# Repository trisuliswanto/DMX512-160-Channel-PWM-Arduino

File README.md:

# DMX512-160-Channel-PWM-Arduino

PCB files for the DMX512-160-Channel-PWM-Arduino

Format is KiCad schematic and board layout
for more information please visit:
  * http://trisuliswanto.com
  
Designed by Tri Suliswanto From Tuban, Jawa Timur, Indonesia.  
GNU GPLv3 license, check LICENSE for more information
All text above must be included in any redistribution

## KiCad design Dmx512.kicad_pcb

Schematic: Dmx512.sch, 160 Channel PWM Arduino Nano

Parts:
A1: Arduino_Nano_v3.x; Arduino_Nano
C11, C12, C13: 4700uF; CP_Radial_D22.0mm_P10.00mm_SnapIn
C14: 10uF; C_0805_2012Metric_Pad1.15x1.40mm_HandSolder
J1: DMX; TerminalBlock_bornier-3_P5.08mm
J13: Screw_Terminal_01x02; TerminalBlock_RND_205-00067_1x02_P7.50mm_Horizontal
R1, R2, R3, R4, R5: 10K; R_0805_2012Metric_Pad1.15x1.40mm_HandSolder
R6, R7: 20K; R_0805_2012Metric_Pad1.15x1.40mm_HandSolder
R8: 120; R_0805_2012Metric_Pad1.15x1.40mm_HandSolder
U1: MAX485E; SO-8_5.3x6.2mm_P1.27mm

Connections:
DERE: A1.5, R4.2, U1.2 (~RE), U1.3 (DE)
GND: A1.4, A1.29, C11.2, C12.2, C13.2, C14.2, J1.3, J13.1, R6.1, U1.5 (GND); also elsewhere on the board
unnamed: J1.1, R6.2, R8.2, U1.7 (B)
unnamed: J1.2, R7.2, R8.1, U1.6 (A)
OE: A1.6; also elsewhere on the board
RXD: A1.2, R5.2, U1.1 (RO)
SCL: A1.24, R1.2; also elsewhere on the board
SDA: A1.23, R2.2; also elsewhere on the board
TXD: A1.1, R3.2, U1.4 (DI)
VCC: A1.27, C11.1, C12.1, C13.1, C14.1, J13.2, R1.1, R2.1, R3.1, R4.1, R5.1, R7.1, U1.8 (VCC); also elsewhere on the board

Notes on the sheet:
DMX RS485
Arduino Nano
Capacitor
PWM IC BLOCK

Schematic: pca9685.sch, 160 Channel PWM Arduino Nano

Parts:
C1: 10uF; C_0805_2012Metric_Pad1.15x1.40mm_HandSolder
D1, D2, D3, D4, D5, D6, D7, D8, D9, D10, D11, D12, D13, D14, D15, D16: LED; LED_D3.0mm
J3: Conn_01x16; PinHeader_1x16_P2.54mm_Vertical
JP1, JP2, JP3, JP4, JP5, JP6: JP; C_0603_1608Metric
R9, R10, R11, R12, R13, R14, R15: 10K; R_0805_2012Metric_Pad1.15x1.40mm_HandSolder
R16, R17, R18, R19, R20, R21, R22, R23, R24, R25, R26, R27, R28, R29, R30, R31: 330; R_0805_2012Metric_Pad1.15x1.40mm_HandSolder
U2: PCA9685PW; TSSOP-28_4.4x9.7mm_P0.65mm

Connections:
/pca9685/LED0: J3.1, R16.2, U2.6
/pca9685/LED1: J3.2, R17.2, U2.7
/pca9685/LED2: J3.3, R18.2, U2.8
/pca9685/LED3: J3.4, R19.2, U2.9
/pca9685/LED4: J3.5, R20.2, U2.10
/pca9685/LED5: J3.6, R21.2, U2.11
/pca9685/LED6: J3.7, R22.2, U2.12
/pca9685/LED7: J3.8, R23.2, U2.13
/pca9685/LED8: J3.9, R24.2, U2.15
/pca9685/LED9: J3.10, R25.2, U2.16
/pca9685/LED10: J3.11, R26.2, U2.17
/pca9685/LED11: J3.12, R27.2, U2.18
/pca9685/LED12: J3.13, R28.2, U2.19
/pca9685/LED13: J3.14, R29.2, U2.20
/pca9685/LED14: J3.15, R30.2, U2.21
/pca9685/LED15: J3.16, R31.2, U2.22
GND: C1.2, R9.1, R10.1, R11.1, R12.1, R13.1, R14.1, R15.2, U2.14, U2.25; also elsewhere on the board
unnamed: D1.1, R16.1
unnamed: D2.1, R17.1
unnamed: D3.1, R18.1
unnamed: D4.1, R19.1
unnamed: D5.1, R20.1
unnamed: D6.1, R21.1
unnamed: D7.1, R22.1
unnamed: D8.1, R23.1
unnamed: D9.1, R24.1
unnamed: D10.1, R25.1
unnamed: D11.1, R26.1
unnamed: D12.1, R27.1
unnamed: D13.1, R28.1
unnamed: D14.1, R29.1
unnamed: D15.1, R30.1
unnamed: D16.1, R31.1
unnamed: JP1.2, R9.2, U2.1
unnamed: JP2.2, R10.2, U2.2
unnamed: JP3.2, R11.2, U2.3
unnamed: JP4.2, R12.2, U2.4
unnamed: JP5.2, R13.2, U2.5
unnamed: JP6.2, R14.2, U2.24
OE: R15.1, U2.23; also elsewhere on the board
SCL: U2.26; also elsewhere on the board
SDA: U2.27; also elsewhere on the board
VCC: C1.1, D1.2, D2.2, D3.2, D4.2, D5.2, D6.2, D7.2, D8.2, D9.2, D10.2, D11.2, D12.2, D13.2, D14.2, D15.2, D16.2, JP1.1, JP2.1, JP3.1, JP4.1, JP5.1, JP6.1, U2.28; also elsewhere on the board

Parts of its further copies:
C2, C3, C4, C5, C6, C7, C8, C9, C10: 10uF; C_0805_2012Metric_Pad1.15x1.40mm_HandSolder
D17, D18, D19, D20, D21, D22, D23, D24, D25, D26, D27, D28, D29, D30, D31, D32, D33, D34, D35, D36, D37, D38, D39, D40, D41, D42, D43, D44, D45, D46, D47, D48, D49, D50, D51, D52, D53, D54, D55, D56, D57, D58, D59, D60, D61, D62, D63, D64, D65, D66, D67, D68, D69, D70, D71, D72, D73, D74, D75, D76, D77, D78, D79, D80, D81, D82, D83, D84, D85, D86, D87, D88, D89, D90, D91, D92, D93, D94, D95, D96, D97, D98, D99, D100, D101, D102, D103, D104, D105, D106, D107, D108, D109, D110, D111, D112, D113, D114, D115, D116, D117, D118, D119, D120, D121, D122, D123, D124, D125, D126, D127, D128, D129, D130, D131, D132, D133, D134, D135, D136, D137, D138, D139, D140, D141, D142, D143, D144, D145, D146, D147, D148, D149, D150, D151, D152, D153, D154, D155, D156, D157, D158, D159, D160: LED; LED_D3.0mm
J4, J5, J6, J7, J8, J9, J10, J11, J12: Conn_01x16; PinHeader_1x16_P2.54mm_Vertical
JP7, JP8, JP9, JP10, JP11, JP12, JP13, JP14, JP15, JP16, JP17, JP18, JP19, JP20, JP21, JP22, JP23, JP24, JP25, JP26, JP27, JP28, JP29, JP30, JP31, JP32, JP33, JP34, JP35, JP36, JP37, JP38, JP39, JP40, JP41, JP42, JP43, JP44, JP45, JP46, JP47, JP48, JP49, JP50, JP51, JP52, JP53, JP54, JP55, JP56, JP57, JP58, JP59, JP60: JP; C_0603_1608Metric
R32, R33, R34, R35, R36, R37, R38, R55, R56, R57, R58, R59, R60, R61, R78, R79, R80, R81, R82, R83, R84, R101, R102, R103, R104, R105, R106, R107, R124, R125, R126, R127, R128, R129, R130, R147, R148, R149, R150, R151, R152, R153, R170, R171, R172, R173, R174, R175, R176, R193, R194, R195, R196, R197, R198, R199, R216, R217, R218, R219, R220, R221, R222: 10K; R_0805_2012Metric_Pad1.15x1.40mm_HandSolder
R39, R40, R41, R42, R43, R44, R45, R46, R47, R48, R49, R50, R51, R52, R53, R54, R62, R63, R64, R65, R66, R67, R68, R69, R70, R71, R72, R73, R74, R75, R76, R77, R85, R86, R87, R88, R89, R90, R91, R92, R93, R94, R95, R96, R97, R98, R99, R100, R108, R109, R110, R111, R112, R113, R114, R115, R116, R117, R118, R119, R120, R121, R122, R123, R131, R132, R133, R134, R135, R136, R137, R138, R139, R140, R141, R142, R143, R144, R145, R146, R154, R155, R156, R157, R158, R159, R160, R161, R162, R163, R164, R165, R166, R167, R168, R169, R177, R178, R179, R180, R181, R182, R183, R184, R185, R186, R187, R188, R189, R190, R191, R192, R200, R201, R202, R203, R204, R205, R206, R207, R208, R209, R210, R211, R212, R213, R214, R215, R223, R224, R225, R226, R227, R228, R229, R230, R231, R232, R233, R234, R235, R236, R237, R238: 330; R_0805_2012Metric_Pad1.15x1.40mm_HandSolder
U3, U4, U5, U6, U7, U8, U9, U10, U11: PCA9685PW; TSSOP-28_4.4x9.7mm_P0.65mm

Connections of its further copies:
/sheet5CDA9F1F/LED0: J4.1, R39.2, U3.6
/sheet5CDA9F1F/LED1: J4.2, R40.2, U3.7
/sheet5CDA9F1F/LED2: J4.3, R41.2, U3.8
/sheet5CDA9F1F/LED3: J4.4, R42.2, U3.9
/sheet5CDA9F1F/LED4: J4.5, R43.2, U3.10
/sheet5CDA9F1F/LED5: J4.6, R44.2, U3.11
/sheet5CDA9F1F/LED6: J4.7, R45.2, U3.12
/sheet5CDA9F1F/LED7: J4.8, R46.2, U3.13
/sheet5CDA9F1F/LED8: J4.9, R47.2, U3.15
/sheet5CDA9F1F/LED9: J4.10, R48.2, U3.16
/sheet5CDA9F1F/LED10: J4.11, R49.2, U3.17
/sheet5CDA9F1F/LED11: J4.12, R50.2, U3.18
/sheet5CDA9F1F/LED12: J4.13, R51.2, U3.19
/sheet5CDA9F1F/LED13: J4.14, R52.2, U3.20
/sheet5CDA9F1F/LED14: J4.15, R53.2, U3.21
/sheet5CDA9F1F/LED15: J4.16, R54.2, U3.22
/sheet5CDAAFF1/LED0: J5.1, R62.2, U4.6
/sheet5CDAAFF1/LED1: J5.2, R63.2, U4.7
/sheet5CDAAFF1/LED2: J5.3, R64.2, U4.8
/sheet5CDAAFF1/LED3: J5.4, R65.2, U4.9
/sheet5CDAAFF1/LED4: J5.5, R66.2, U4.10
/sheet5CDAAFF1/LED5: J5.6, R67.2, U4.11
/sheet5CDAAFF1/LED6: J5.7, R68.2, U4.12
/sheet5CDAAFF1/LED7: J5.8, R69.2, U4.13
/sheet5CDAAFF1/LED8: J5.9, R70.2, U4.15
/sheet5CDAAFF1/LED9: J5.10, R71.2, U4.16
/sheet5CDAAFF1/LED10: J5.11, R72.2, U4.17
/sheet5CDAAFF1/LED11: J5.12, R73.2, U4.18
/sheet5CDAAFF1/LED12: J5.13, R74.2, U4.19
/sheet5CDAAFF1/LED13: J5.14, R75.2, U4.20
/sheet5CDAAFF1/LED14: J5.15, R76.2, U4.21
/sheet5CDAAFF1/LED15: J5.16, R77.2, U4.22
/sheet5CDAC124/LED0: J6.1, R85.2, U5.6
/sheet5CDAC124/LED1: J6.2, R86.2, U5.7
/sheet5CDAC124/LED2: J6.3, R87.2, U5.8
/sheet5CDAC124/LED3: J6.4, R88.2, U5.9
/sheet5CDAC124/LED4: J6.5, R89.2, U5.10
/sheet5CDAC124/LED5: J6.6, R90.2, U5.11
/sheet5CDAC124/LED6: J6.7, R91.2, U5.12
/sheet5CDAC124/LED7: J6.8, R92.2, U5.13
/sheet5CDAC124/LED8: J6.9, R93.2, U5.15
/sheet5CDAC124/LED9: J6.10, R94.2, U5.16
/sheet5CDAC124/LED10: J6.11, R95.2, U5.17
/sheet5CDAC124/LED11: J6.12, R96.2, U5.18
/sheet5CDAC124/LED12: J6.13, R97.2, U5.19
/sheet5CDAC124/LED13: J6.14, R98.2, U5.20
/sheet5CDAC124/LED14: J6.15, R99.2, U5.21
/sheet5CDAC124/LED15: J6.16, R100.2, U5.22
/sheet5CDCB530/LED0: J7.1, R108.2, U6.6
/sheet5CDCB530/LED1: J7.2, R109.2, U6.7
/sheet5CDCB530/LED2: J7.3, R110.2, U6.8
/sheet5CDCB530/LED3: J7.4, R111.2, U6.9
/sheet5CDCB530/LED4: J7.5, R112.2, U6.10
/sheet5CDCB530/LED5: J7.6, R113.2, U6.11
/sheet5CDCB530/LED6: J7.7, R114.2, U6.12
/sheet5CDCB530/LED7: J7.8, R115.2, U6.13
/sheet5CDCB530/LED8: J7.9, R116.2, U6.15
/sheet5CDCB530/LED9: J7.10, R117.2, U6.16
/sheet5CDCB530/LED10: J7.11, R118.2, U6.17
/sheet5CDCB530/LED11: J7.12, R119.2, U6.18
/sheet5CDCB530/LED12: J7.13, R120.2, U6.19
/sheet5CDCB530/LED13: J7.14, R121.2, U6.20
/sheet5CDCB530/LED14: J7.15, R122.2, U6.21
/sheet5CDCB530/LED15: J7.16, R123.2, U6.22
/sheet5CDCD3B7/LED0: J8.1, R131.2, U7.6
/sheet5CDCD3B7/LED1: J8.2, R132.2, U7.7
/sheet5CDCD3B7/LED2: J8.3, R133.2, U7.8
/sheet5CDCD3B7/LED3: J8.4, R134.2, U7.9
/sheet5CDCD3B7/LED4: J8.5, R135.2, U7.10
/sheet5CDCD3B7/LED5: J8.6, R136.2, U7.11
/sheet5CDCD3B7/LED6: J8.7, R137.2, U7.12
/sheet5CDCD3B7/LED7: J8.8, R138.2, U7.13
/sheet5CDCD3B7/LED8: J8.9, R139.2, U7.15
/sheet5CDCD3B7/LED9: J8.10, R140.2, U7.16
/sheet5CDCD3B7/LED10: J8.11, R141.2, U7.17
/sheet5CDCD3B7/LED11: J8.12, R142.2, U7.18
/sheet5CDCD3B7/LED12: J8.13, R143.2, U7.19
/sheet5CDCD3B7/LED13: J8.14, R144.2, U7.20
/sheet5CDCD3B7/LED14: J8.15, R145.2, U7.21
/sheet5CDCD3B7/LED15: J8.16, R146.2, U7.22
/sheet5CDCD3BF/LED0: J9.1, R154.2, U8.6
/sheet5CDCD3BF/LED1: J9.2, R155.2, U8.7
/sheet5CDCD3BF/LED2: J9.3, R156.2, U8.8
/sheet5CDCD3BF/LED3: J9.4, R157.2, U8.9
/sheet5CDCD3BF/LED4: J9.5, R158.2, U8.10
/sheet5CDCD3BF/LED5: J9.6, R159.2, U8.11
/sheet5CDCD3BF/LED6: J9.7, R160.2, U8.12
/sheet5CDCD3BF/LED7: J9.8, R161.2, U8.13
/sheet5CDCD3BF/LED8: J9.9, R162.2, U8.15
/sheet5CDCD3BF/LED9: J9.10, R163.2, U8.16
/sheet5CDCD3BF/LED10: J9.11, R164.2, U8.17
/sheet5CDCD3BF/LED11: J9.12, R165.2, U8.18
/sheet5CDCD3BF/LED12: J9.13, R166.2, U8.19
/sheet5CDCD3BF/LED13: J9.14, R167.2, U8.20
/sheet5CDCD3BF/LED14: J9.15, R168.2, U8.21
/sheet5CDCD3BF/LED15: J9.16, R169.2, U8.22
/sheet5CDCD3C7/LED0: J10.1, R177.2, U9.6
/sheet5CDCD3C7/LED1: J10.2, R178.2, U9.7
/sheet5CDCD3C7/LED2: J10.3, R179.2, U9.8
/sheet5CDCD3C7/LED3: J10.4, R180.2, U9.9
/sheet5CDCD3C7/LED4: J10.5, R181.2, U9.10
/sheet5CDCD3C7/LED5: J10.6, R182.2, U9.11
/sheet5CDCD3C7/LED6: J10.7, R183.2, U9.12
/sheet5CDCD3C7/LED7: J10.8, R184.2, U9.13
/sheet5CDCD3C7/LED8: J10.9, R185.2, U9.15
/sheet5CDCD3C7/LED9: J10.10, R186.2, U9.16
/sheet5CDCD3C7/LED10: J10.11, R187.2, U9.17
/sheet5CDCD3C7/LED11: J10.12, R188.2, U9.18
/sheet5CDCD3C7/LED12: J10.13, R189.2, U9.19
/sheet5CDCD3C7/LED13: J10.14, R190.2, U9.20
/sheet5CDCD3C7/LED14: J10.15, R191.2, U9.21
/sheet5CDCD3C7/LED15: J10.16, R192.2, U9.22
/sheet5CDCD3CF/LED0: J11.1, R200.2, U10.6
/sheet5CDCD3CF/LED1: J11.2, R201.2, U10.7
/sheet5CDCD3CF/LED2: J11.3, R202.2, U10.8
/sheet5CDCD3CF/LED3: J11.4, R203.2, U10.9
/sheet5CDCD3CF/LED4: J11.5, R204.2, U10.10
/sheet5CDCD3CF/LED5: J11.6, R205.2, U10.11
/sheet5CDCD3CF/LED6: J11.7, R206.2, U10.12
/sheet5CDCD3CF/LED7: J11.8, R207.2, U10.13
/sheet5CDCD3CF/LED8: J11.9, R208.2, U10.15
/sheet5CDCD3CF/LED9: J11.10, R209.2, U10.16
/sheet5CDCD3CF/LED10: J11.11, R210.2, U10.17
/sheet5CDCD3CF/LED11: J11.12, R211.2, U10.18
/sheet5CDCD3CF/LED12: J11.13, R212.2, U10.19
/sheet5CDCD3CF/LED13: J11.14, R213.2, U10.20
/sheet5CDCD3CF/LED14: J11.15, R214.2, U10.21
/sheet5CDCD3CF/LED15: J11.16, R215.2, U10.22
/sheet5CDCD3D7/LED0: J12.1, R223.2, U11.6
/sheet5CDCD3D7/LED1: J12.2, R224.2, U11.7
/sheet5CDCD3D7/LED2: J12.3, R225.2, U11.8
/sheet5CDCD3D7/LED3: J12.4, R226.2, U11.9
/sheet5CDCD3D7/LED4: J12.5, R227.2, U11.10
/sheet5CDCD3D7/LED5: J12.6, R228.2, U11.11
/sheet5CDCD3D7/LED6: J12.7, R229.2, U11.12
/sheet5CDCD3D7/LED7: J12.8, R230.2, U11.13
/sheet5CDCD3D7/LED8: J12.9, R231.2, U11.15
/sheet5CDCD3D7/LED9: J12.10, R232.2, U11.16
/sheet5CDCD3D7/LED10: J12.11, R233.2, U11.17
/sheet5CDCD3D7/LED11: J12.12, R234.2, U11.18
/sheet5CDCD3D7/LED12: J12.13, R235.2, U11.19
/sheet5CDCD3D7/LED13: J12.14, R236.2, U11.20
/sheet5CDCD3D7/LED14: J12.15, R237.2, U11.21
/sheet5CDCD3D7/LED15: J12.16, R238.2, U11.22
GND: C2.2, C3.2, C4.2, C5.2, C6.2, C7.2, C8.2, C9.2, C10.2, R32.1, R33.1, R34.1, R35.1, R36.1, R37.1, R38.2, R55.1, R56.1, R57.1, R58.1, R59.1, R60.1, R61.2, R78.1, R79.1, R80.1, R81.1, R82.1, R83.1, R84.2, R101.1, R102.1, R103.1, R104.1, R105.1, R106.1, R107.2, R124.1, R125.1, R126.1, R127.1, R128.1, R129.1, R130.2, R147.1, R148.1, R149.1, R150.1, R151.1, R152.1, R153.2, R170.1, R171.1, R172.1, R173.1, R174.1, R175.1, R176.2, R193.1, R194.1, R195.1, R196.1, R197.1, R198.1, R199.2, R216.1, R217.1, R218.1, R219.1, R220.1, R221.1, R222.2, U3.14, U3.25, U4.14, U4.25, U5.14, U5.25, U6.14, U6.25, U7.14, U7.25, U8.14, U8.25, U9.14, U9.25, U10.14, U10.25, U11.14, U11.25; also elsewhere on the board
unnamed: D17.1, R39.1
unnamed: D18.1, R40.1
unnamed: D19.1, R41.1
unnamed: D20.1, R42.1
unnamed: D21.1, R43.1
unnamed: D22.1, R44.1
unnamed: D23.1, R45.1
unnamed: D24.1, R46.1
unnamed: D25.1, R47.1
unnamed: D26.1, R48.1
unnamed: D27.1, R49.1
unnamed: D28.1, R50.1
unnamed: D29.1, R51.1
unnamed: D30.1, R52.1
unnamed: D31.1, R53.1
unnamed: D32.1, R54.1
unnamed: D33.1, R62.1
unnamed: D34.1, R63.1
unnamed: D35.1, R64.1
unnamed: D36.1, R65.1
unnamed: D37.1, R66.1
unnamed: D38.1, R67.1
unnamed: D39.1, R68.1
unnamed: D40.1, R69.1
unnamed: D41.1, R70.1
unnamed: D42.1, R71.1
unnamed: D43.1, R72.1
unnamed: D44.1, R73.1
unnamed: D45.1, R74.1
unnamed: D46.1, R75.1
unnamed: D47.1, R76.1
unnamed: D48.1, R77.1
unnamed: D49.1, R85.1
unnamed: D50.1, R86.1
unnamed: D51.1, R87.1
unnamed: D52.1, R88.1
unnamed: D53.1, R89.1
unnamed: D54.1, R90.1
unnamed: D55.1, R91.1
unnamed: D56.1, R92.1
unnamed: D57.1, R93.1
unnamed: D58.1, R94.1
unnamed: D59.1, R95.1
unnamed: D60.1, R96.1
unnamed: D61.1, R97.1
unnamed: D62.1, R98.1
unnamed: D63.1, R99.1
unnamed: D64.1, R100.1
unnamed: D65.1, R108.1
unnamed: D66.1, R109.1
unnamed: D67.1, R110.1
unnamed: D68.1, R111.1
unnamed: D69.1, R112.1
unnamed: D70.1, R113.1
unnamed: D71.1, R114.1
unnamed: D72.1, R115.1
unnamed: D73.1, R116.1
unnamed: D74.1, R117.1
unnamed: D75.1, R118.1
unnamed: D76.1, R119.1
unnamed: D77.1, R120.1
unnamed: D78.1, R121.1
unnamed: D79.1, R122.1
unnamed: D80.1, R123.1
unnamed: D81.1, R131.1
unnamed: D82.1, R132.1
unnamed: D83.1, R133.1
unnamed: D84.1, R134.1
unnamed: D85.1, R135.1
unnamed: D86.1, R136.1
unnamed: D87.1, R137.1
unnamed: D88.1, R138.1
unnamed: D89.1, R139.1
unnamed: D90.1, R140.1
unnamed: D91.1, R141.1
unnamed: D92.1, R142.1
unnamed: D93.1, R143.1
unnamed: D94.1, R144.1
unnamed: D95.1, R145.1
unnamed: D96.1, R146.1
unnamed: D97.1, R154.1
unnamed: D98.1, R155.1
unnamed: D99.1, R156.1
unnamed: D100.1, R157.1
unnamed: D101.1, R158.1
unnamed: D102.1, R159.1
unnamed: D103.1, R160.1
unnamed: D104.1, R161.1
unnamed: D105.1, R162.1
unnamed: D106.1, R163.1
unnamed: D107.1, R164.1
unnamed: D108.1, R165.1
unnamed: D109.1, R166.1
unnamed: D110.1, R167.1
unnamed: D111.1, R168.1
unnamed: D112.1, R169.1
unnamed: D113.1, R177.1
unnamed: D114.1, R178.1
unnamed: D115.1, R179.1
unnamed: D116.1, R180.1
unnamed: D117.1, R181.1
unnamed: D118.1, R182.1
unnamed: D119.1, R183.1
unnamed: D120.1, R184.1
unnamed: D121.1, R185.1
unnamed: D122.1, R186.1
unnamed: D123.1, R187.1
unnamed: D124.1, R188.1
unnamed: D125.1, R189.1
unnamed: D126.1, R190.1
unnamed: D127.1, R191.1
unnamed: D128.1, R192.1
unnamed: D129.1, R200.1
unnamed: D130.1, R201.1
unnamed: D131.1, R202.1
unnamed: D132.1, R203.1
unnamed: D133.1, R204.1
unnamed: D134.1, R205.1
unnamed: D135.1, R206.1
unnamed: D136.1, R207.1
unnamed: D137.1, R208.1
unnamed: D138.1, R209.1
unnamed: D139.1, R210.1
unnamed: D140.1, R211.1
unnamed: D141.1, R212.1
unnamed: D142.1, R213.1
unnamed: D143.1, R214.1
unnamed: D144.1, R215.1
unnamed: D145.1, R223.1
unnamed: D146.1, R224.1
unnamed: D147.1, R225.1
unnamed: D148.1, R226.1
unnamed: D149.1, R227.1
unnamed: D150.1, R228.1
unnamed: D151.1, R229.1
unnamed: D152.1, R230.1
unnamed: D153.1, R231.1
unnamed: D154.1, R232.1
unnamed: D155.1, R233.1
unnamed: D156.1, R234.1
unnamed: D157.1, R235.1
unnamed: D158.1, R236.1
unnamed: D159.1, R237.1
unnamed: D160.1, R238.1
unnamed: JP7.2, R32.2, U3.1
unnamed: JP8.2, R33.2, U3.2
unnamed: JP9.2, R34.2, U3.3
unnamed: JP10.2, R35.2, U3.4
unnamed: JP11.2, R36.2, U3.5
unnamed: JP12.2, R37.2, U3.24
unnamed: JP13.2, R55.2, U4.1
unnamed: JP14.2, R56.2, U4.2
unnamed: JP15.2, R57.2, U4.3
unnamed: JP16.2, R58.2, U4.4
unnamed: JP17.2, R59.2, U4.5
unnamed: JP18.2, R60.2, U4.24
unnamed: JP19.2, R78.2, U5.1
unnamed: JP20.2, R79.2, U5.2
unnamed: JP21.2, R80.2, U5.3
unnamed: JP22.2, R81.2, U5.4
unnamed: JP23.2, R82.2, U5.5
unnamed: JP24.2, R83.2, U5.24
unnamed: JP25.2, R101.2, U6.1
unnamed: JP26.2, R102.2, U6.2
unnamed: JP27.2, R103.2, U6.3
unnamed: JP28.2, R104.2, U6.4
unnamed: JP29.2, R105.2, U6.5
unnamed: JP30.2, R106.2, U6.24
unnamed: JP31.2, R124.2, U7.1
unnamed: JP32.2, R125.2, U7.2
unnamed: JP33.2, R126.2, U7.3
unnamed: JP34.2, R127.2, U7.4
unnamed: JP35.2, R128.2, U7.5
unnamed: JP36.2, R129.2, U7.24
unnamed: JP37.2, R147.2, U8.1
unnamed: JP38.2, R148.2, U8.2
unnamed: JP39.2, R149.2, U8.3
unnamed: JP40.2, R150.2, U8.4
unnamed: JP41.2, R151.2, U8.5
unnamed: JP42.2, R152.2, U8.24
unnamed: JP43.2, R170.2, U9.1
unnamed: JP44.2, R171.2, U9.2
unnamed: JP45.2, R172.2, U9.3
unnamed: JP46.2, R173.2, U9.4
unnamed: JP47.2, R174.2, U9.5
unnamed: JP48.2, R175.2, U9.24
unnamed: JP49.2, R193.2, U10.1
unnamed: JP50.2, R194.2, U10.2
unnamed: JP51.2, R195.2, U10.3
unnamed: JP52.2, R196.2, U10.4
unnamed: JP53.2, R197.2, U10.5
unnamed: JP54.2, R198.2, U10.24
unnamed: JP55.2, R216.2, U11.1
unnamed: JP56.2, R217.2, U11.2
unnamed: JP57.2, R218.2, U11.3
unnamed: JP58.2, R219.2, U11.4
unnamed: JP59.2, R220.2, U11.5
unnamed: JP60.2, R221.2, U11.24
OE: R38.1, R61.1, R84.1, R107.1, R130.1, R153.1, R176.1, R199.1, R222.1, U3.23, U4.23, U5.23, U6.23, U7.23, U8.23, U9.23, U10.23, U11.23; also elsewhere on the board
SCL: U3.26, U4.26, U5.26, U6.26, U7.26, U8.26, U9.26, U10.26, U11.26; also elsewhere on the board
SDA: U3.27, U4.27, U5.27, U6.27, U7.27, U8.27, U9.27, U10.27, U11.27; also elsewhere on the board
VCC: C2.1, C3.1, C4.1, C5.1, C6.1, C7.1, C8.1, C9.1, C10.1, D17.2, D18.2, D19.2, D20.2, D21.2, D22.2, D23.2, D24.2, D25.2, D26.2, D27.2, D28.2, D29.2, D30.2, D31.2, D32.2, D33.2, D34.2, D35.2, D36.2, D37.2, D38.2, D39.2, D40.2, D41.2, D42.2, D43.2, D44.2, D45.2, D46.2, D47.2, D48.2, D49.2, D50.2, D51.2, D52.2, D53.2, D54.2, D55.2, D56.2, D57.2, D58.2, D59.2, D60.2, D61.2, D62.2, D63.2, D64.2, D65.2, D66.2, D67.2, D68.2, D69.2, D70.2, D71.2, D72.2, D73.2, D74.2, D75.2, D76.2, D77.2, D78.2, D79.2, D80.2, D81.2, D82.2, D83.2, D84.2, D85.2, D86.2, D87.2, D88.2, D89.2, D90.2, D91.2, D92.2, D93.2, D94.2, D95.2, D96.2, D97.2, D98.2, D99.2, D100.2, D101.2, D102.2, D103.2, D104.2, D105.2, D106.2, D107.2, D108.2, D109.2, D110.2, D111.2, D112.2, D113.2, D114.2, D115.2, D116.2, D117.2, D118.2, D119.2, D120.2, D121.2, D122.2, D123.2, D124.2, D125.2, D126.2, D127.2, D128.2, D129.2, D130.2, D131.2, D132.2, D133.2, D134.2, D135.2, D136.2, D137.2, D138.2, D139.2, D140.2, D141.2, D142.2, D143.2, D144.2, D145.2, D146.2, D147.2, D148.2, D149.2, D150.2, D151.2, D152.2, D153.2, D154.2, D155.2, D156.2, D157.2, D158.2, D159.2, D160.2, JP7.1, JP8.1, JP9.1, JP10.1, JP11.1, JP12.1, JP13.1, JP14.1, JP15.1, JP16.1, JP17.1, JP18.1, JP19.1, JP20.1, JP21.1, JP22.1, JP23.1, JP24.1, JP25.1, JP26.1, JP27.1, JP28.1, JP29.1, JP30.1, JP31.1, JP32.1, JP33.1, JP34.1, JP35.1, JP36.1, JP37.1, JP38.1, JP39.1, JP40.1, JP41.1, JP42.1, JP43.1, JP44.1, JP45.1, JP46.1, JP47.1, JP48.1, JP49.1, JP50.1, JP51.1, JP52.1, JP53.1, JP54.1, JP55.1, JP56.1, JP57.1, JP58.1, JP59.1, JP60.1, U3.28, U4.28, U5.28, U6.28, U7.28, U8.28, U9.28, U10.28, U11.28; also elsewhere on the board

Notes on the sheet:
I2C Address =
1 + A5 + A4 + A3 + A2 + A1 +A1 + RW
Open = 0 / Closed = 1

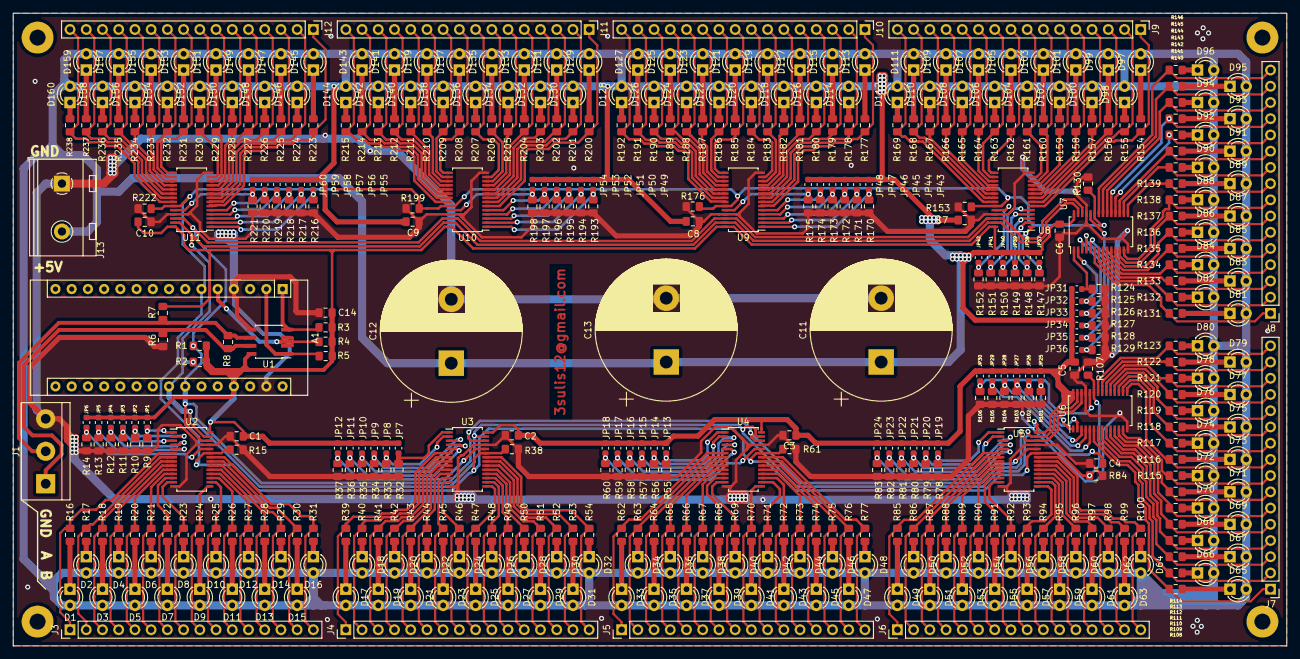
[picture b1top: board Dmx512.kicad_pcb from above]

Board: 2 copper layers, 199.4 x 99.1 mm, 496 parts (0 on the bottom side), 390 nets.

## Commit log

2019-05-18 initial Release
2019-05-18 Create LICENSE
2019-05-18 add screensshot
